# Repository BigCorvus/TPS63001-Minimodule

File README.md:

# TPS63001-Minimodule
Small breakout for the TPS63001 - a 1.8-5.5V in and 3.3V out buck boost converter by TI

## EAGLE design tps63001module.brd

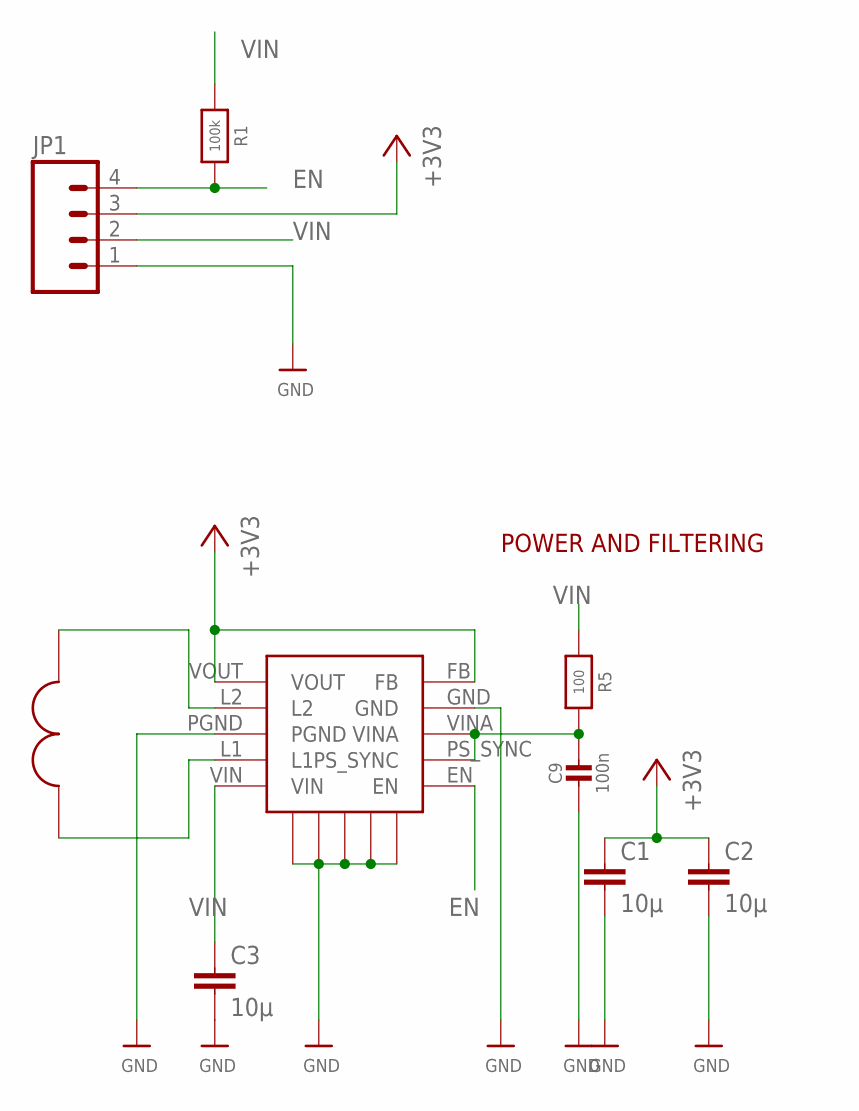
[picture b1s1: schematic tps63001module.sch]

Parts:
C1, C2, C3: 10µ; C0805
C9: 100n; 0603-NO
JP1: M04PTH; 1X04
R1: 100k; 0603-NO
R5: 100; 0603-NO
U$12: TPS63001
U$15: VLF4012A

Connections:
+3V3: C1.1, C2.1, JP1.3, U$12.FB, U$12.VOUT
EN: JP1.4, R1.2, U$12.EN
GND: C1.2, C2.2, C3.2, C9.2, JP1.1, U$12.GND, U$12.GNDP1, U$12.GNDP2, U$12.GNDP3, U$12.GNDP4, U$12.GNDP5, U$12.PGND
unnamed: U$12.L1, U$15.P$1
unnamed: U$12.L2, U$15.P$2
VIN: C3.1, JP1.2, R1.1, R5.1, U$12.VIN
VINA_ETC: C9.1, R5.2, U$12.PS_SYNC, U$12.VINA

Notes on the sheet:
POWER AND FILTERING

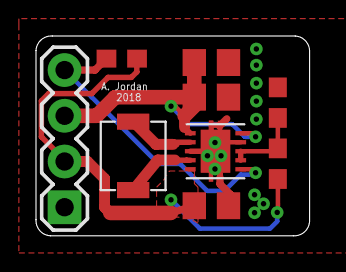
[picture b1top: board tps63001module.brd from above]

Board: 2 copper layers, 15.2 x 11.1 mm, 9 parts (0 on the bottom side), 7 nets.

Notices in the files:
parts and their libraries:
microbuilder: This work is placed in the public domain, and may be freely used for commercial and non-commercial work with the following conditions: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
SparkFun-Connectors: Licensing: Creative Commons ShareAlike 4.0 International - https://creativecommons.org/licenses/by-sa/4.0
